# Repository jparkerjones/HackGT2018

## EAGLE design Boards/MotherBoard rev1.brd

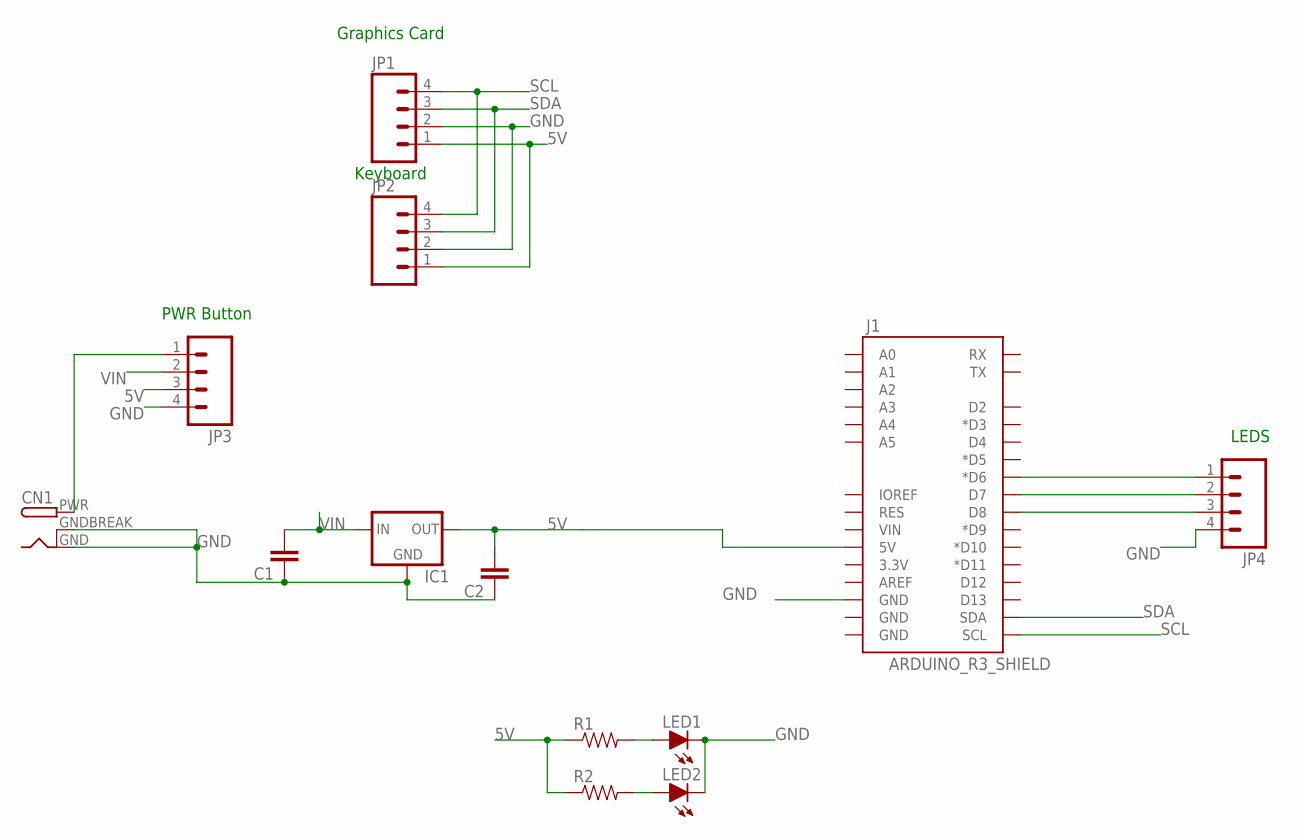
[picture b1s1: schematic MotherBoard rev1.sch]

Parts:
C1, C2: CAPPTH3; CAP-PTH-LARGE
CN1: DCBARRELPTH; DCJACK_2MM_PTH
IC1: 5VREG_L7805SPACED; TO-220-SPACED
J1: ARDUINO_R3_SHIELD; UNO_R3_SHIELD
JP1, JP2, JP3, JP4: M04; 1X04
LED1, LED2: LED-5MM
R1, R2: RESISTORPTH-1/2W; AXIAL-0.5

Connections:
5V: C2.2, IC1.3 (OUT), J1.5V, JP1.1, JP2.1, JP3.3, R1.P$1 (1), R2.P$1 (1)
GND: C1.1, C2.1, CN1.GND, CN1.GNDBREAK, IC1.2 (GND), J1.GND@2 (GND), JP1.2, JP2.2, JP3.4, JP4.4, LED1.K (C), LED2.K (C)
unnamed: LED1.A, R1.P$2 (2)
unnamed: LED2.A, R2.P$2 (2)
unnamed: CN1.PWR, JP3.1
unnamed: J1.D8, JP4.3
unnamed: J1.D6 (*D6), JP4.1
unnamed: J1.D7, JP4.2
SCL: J1.SCL, JP1.4, JP2.4
SDA: J1.SDA, JP1.3, JP2.3
VIN: C1.2, IC1.1 (IN), JP3.2

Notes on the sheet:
Graphics Card
Keyboard
PWR Button
LEDS

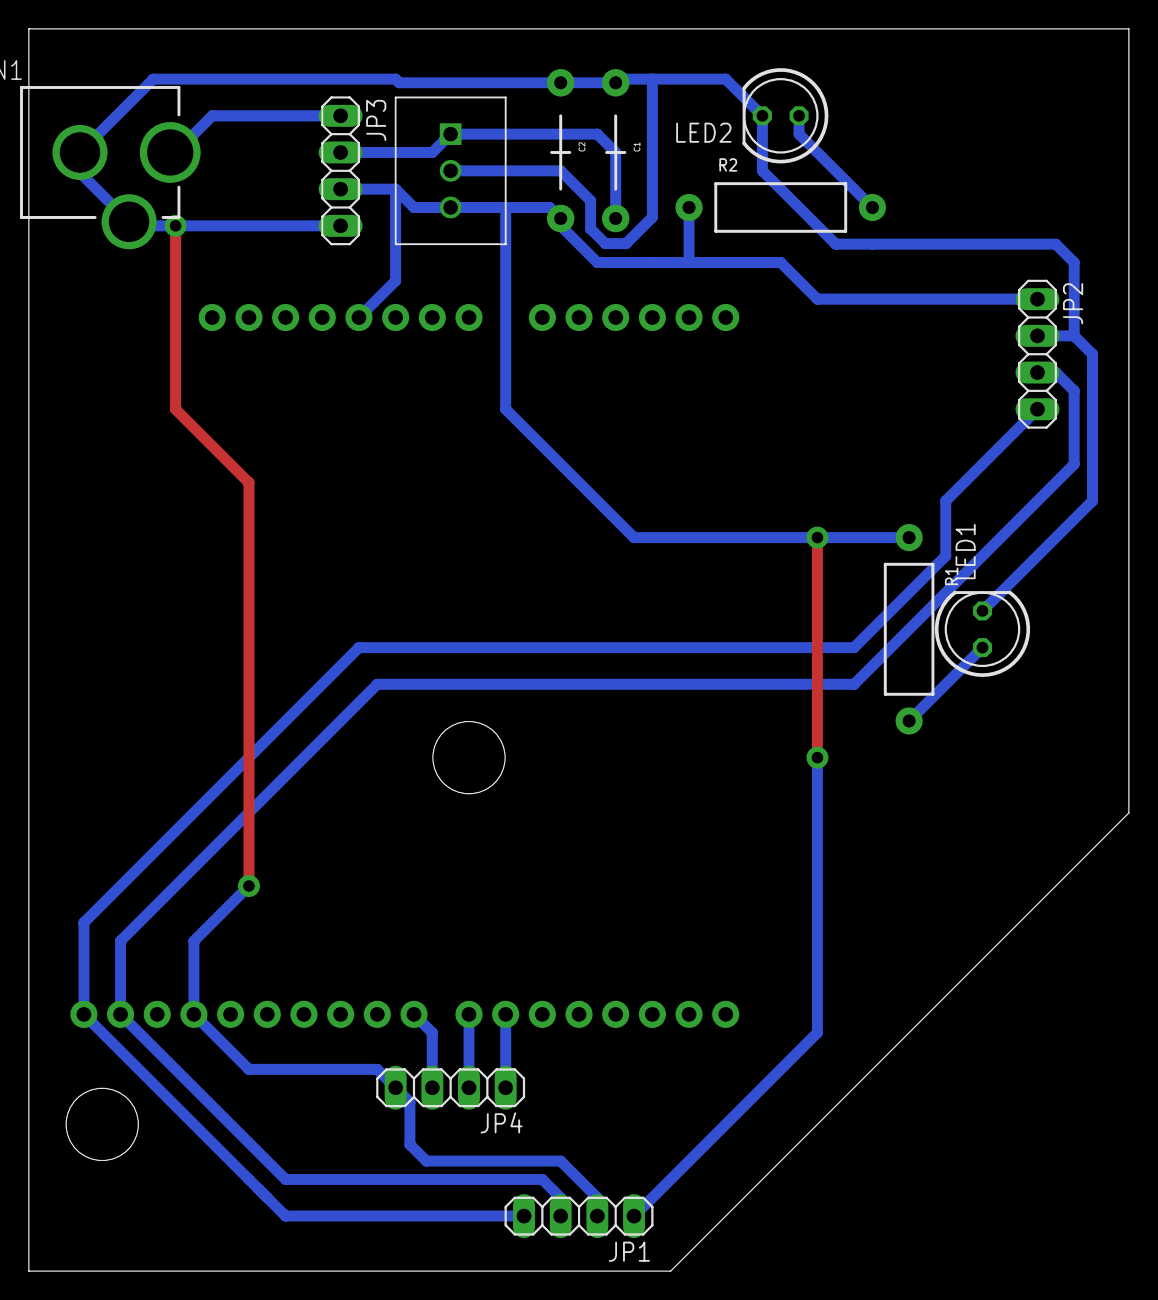
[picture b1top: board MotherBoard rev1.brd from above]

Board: 2 copper layers, 76.2 x 86.0 mm, 13 parts (1 on the bottom side), 11 nets.

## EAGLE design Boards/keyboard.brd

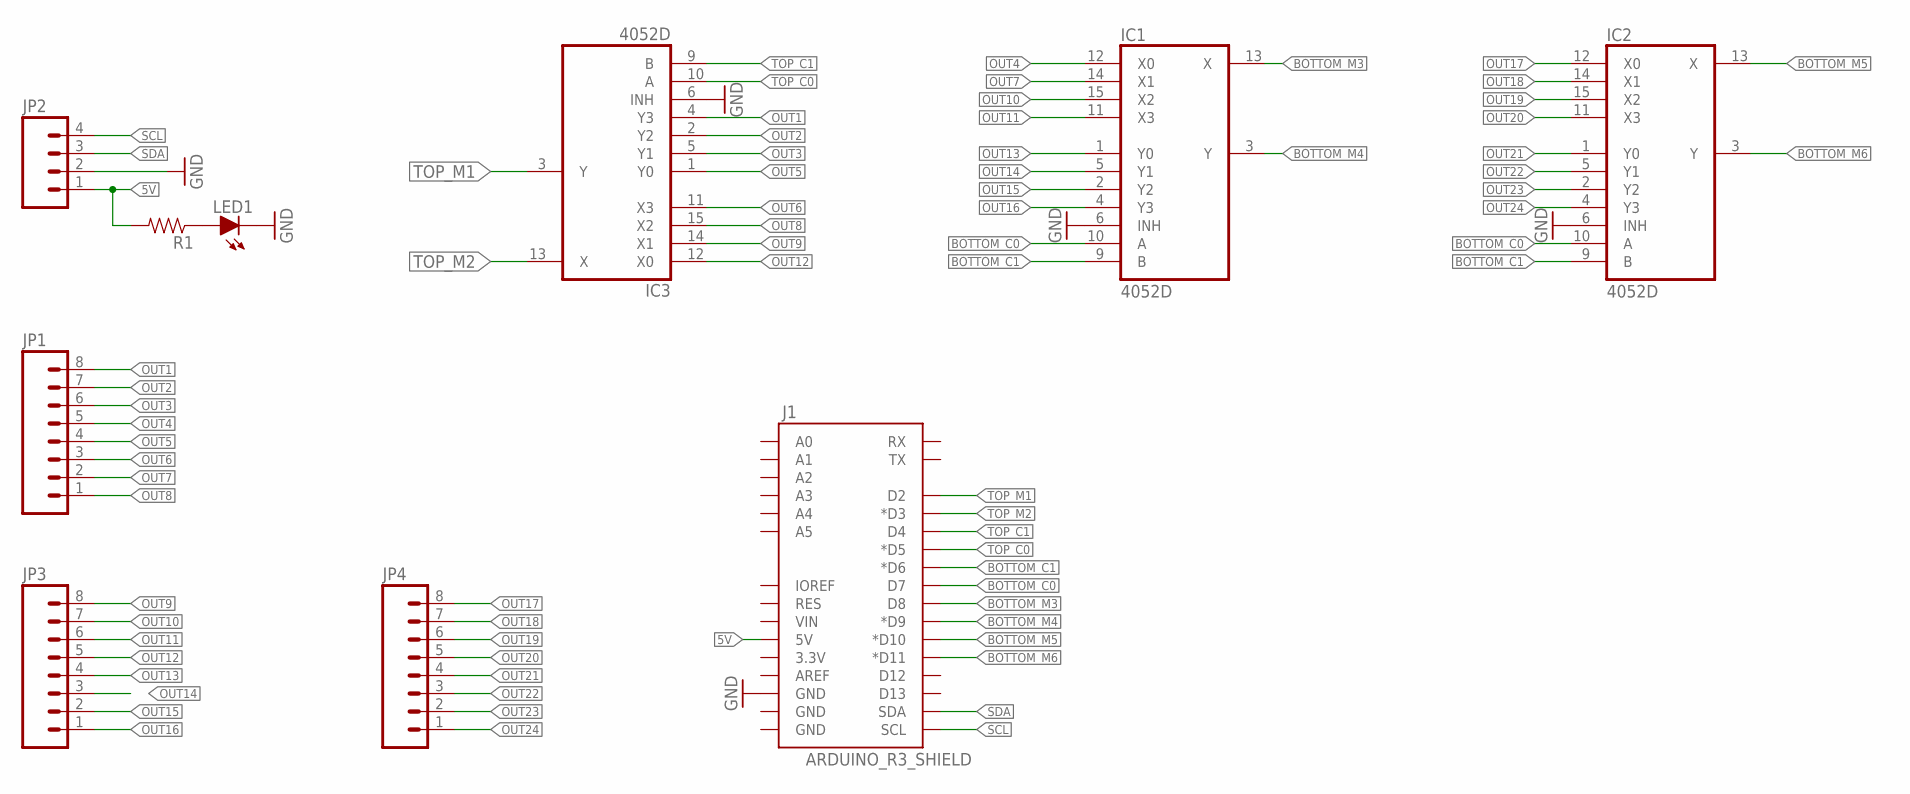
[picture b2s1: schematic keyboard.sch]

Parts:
IC1, IC2, IC3: 4052D; SO16
J1: ARDUINO_R3_SHIELD; UNO_R3_SHIELD
JP1, JP3, JP4: M08; 1X08
JP2: M04; 1X04
LED1: LED-5MM
R1: RESISTORPTH-1/2W; AXIAL-0.5

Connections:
5V: J1.5V, JP2.1, R1.P$2 (2)
BOTTOM_C0: IC1.10 (A), IC2.10 (A), J1.D7
BOTTOM_C1: IC1.9 (B), IC2.9 (B), J1.D6 (*D6)
BOTTOM_M3: IC1.13 (X), J1.D8
BOTTOM_M4: IC1.3 (Y), J1.D9 (*D9)
BOTTOM_M5: IC2.13 (X), J1.D10 (*D10)
BOTTOM_M6: IC2.3 (Y), J1.D11 (*D11)
GND: IC1.6 (INH), IC1.8 (GND), IC2.6 (INH), IC2.8 (GND), IC3.6 (INH), IC3.8 (GND), J1.GND@2 (GND), JP2.2, LED1.K (C)
unnamed: LED1.A, R1.P$1 (1)
OUT1: IC3.4 (Y3), JP1.8
OUT2: IC3.2 (Y2), JP1.7
OUT3: IC3.5 (Y1), JP1.6
OUT4: IC1.12 (X0), JP1.5
OUT5: IC3.1 (Y0), JP1.4
OUT6: IC3.11 (X3), JP1.3
OUT7: IC1.14 (X1), JP1.2
OUT8: IC3.15 (X2), JP1.1
OUT9: IC3.14 (X1), JP3.8
OUT10: IC1.15 (X2), JP3.7
OUT11: IC1.11 (X3), JP3.6
OUT12: IC3.12 (X0), JP3.5
OUT13: IC1.1 (Y0), JP3.4
OUT14: IC1.5 (Y1), JP3.3
OUT15: IC1.2 (Y2), JP3.2
OUT16: IC1.4 (Y3), JP3.1
OUT17: IC2.12 (X0), JP4.8
OUT18: IC2.14 (X1), JP4.7
OUT19: IC2.15 (X2), JP4.6
OUT20: IC2.11 (X3), JP4.5
OUT21: IC2.1 (Y0), JP4.4
OUT22: IC2.5 (Y1), JP4.3
OUT23: IC2.2 (Y2), JP4.2
OUT24: IC2.4 (Y3), JP4.1
SCL: J1.SCL, JP2.4
SDA: J1.SDA, JP2.3
TOP_C0: IC3.10 (A), J1.D5 (*D5)
TOP_C1: IC3.9 (B), J1.D4
TOP_M1: IC3.3 (Y), J1.D2
TOP_M2: IC3.13 (X), J1.D3 (*D3)
VCC: IC1.16 (VCC), IC2.16 (VCC), IC3.16 (VCC)
VEE: IC1.7 (VEE), IC2.7 (VEE), IC3.7 (VEE)

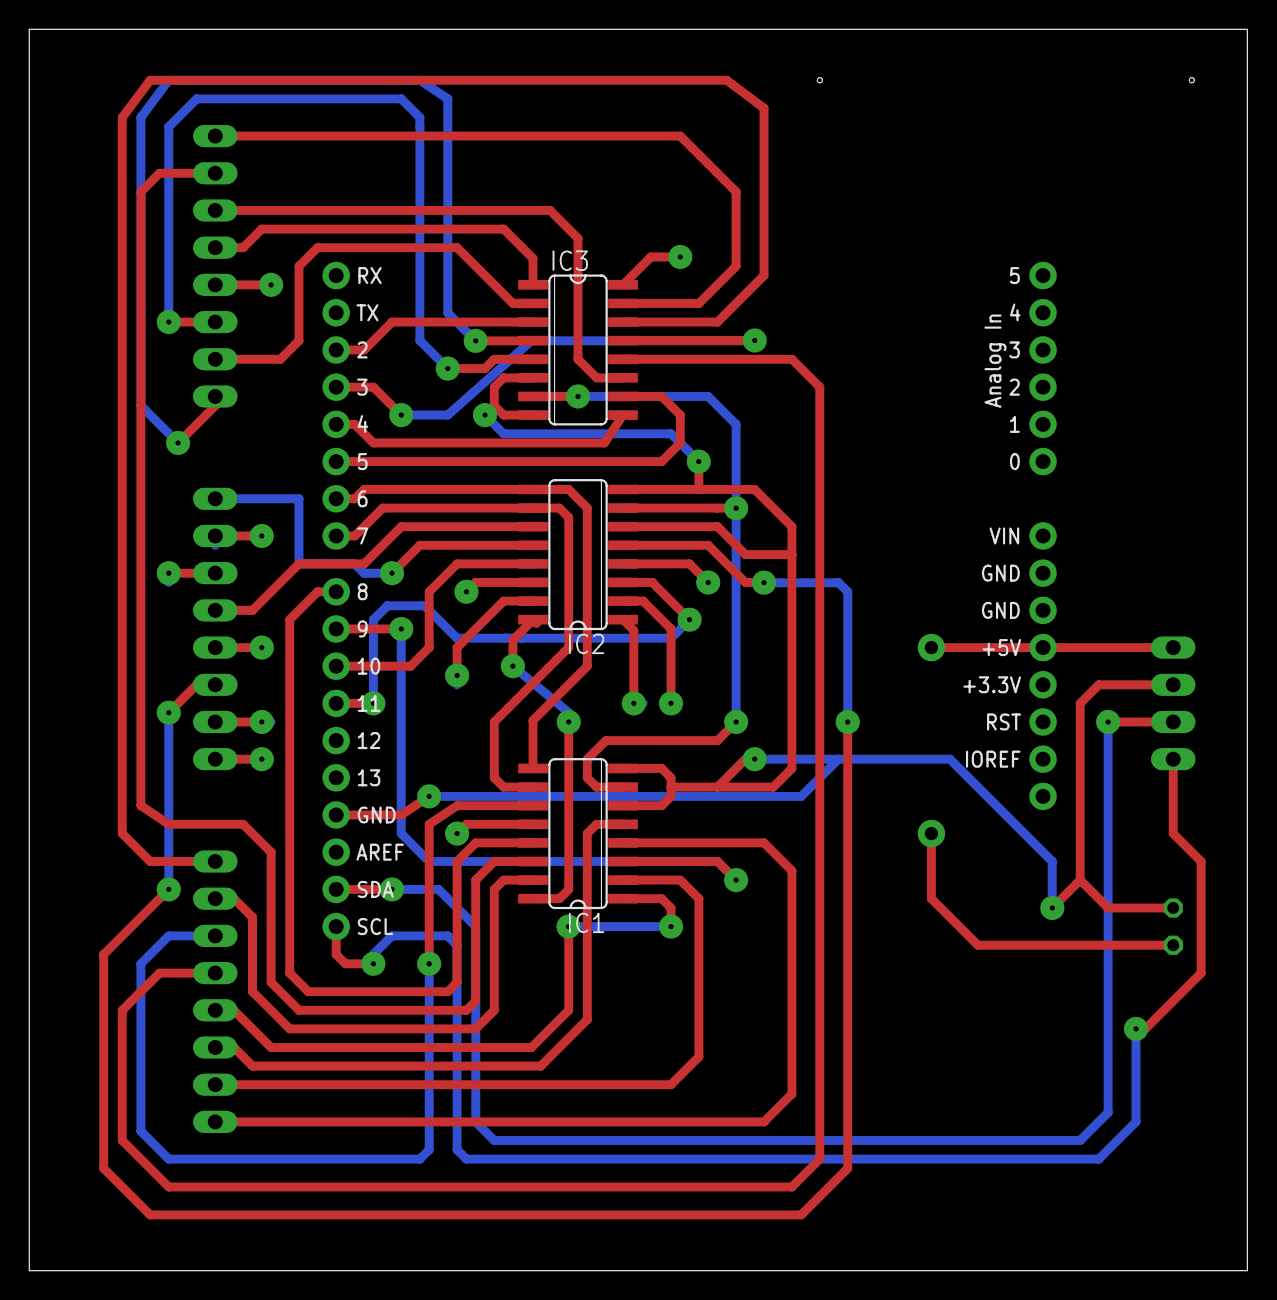
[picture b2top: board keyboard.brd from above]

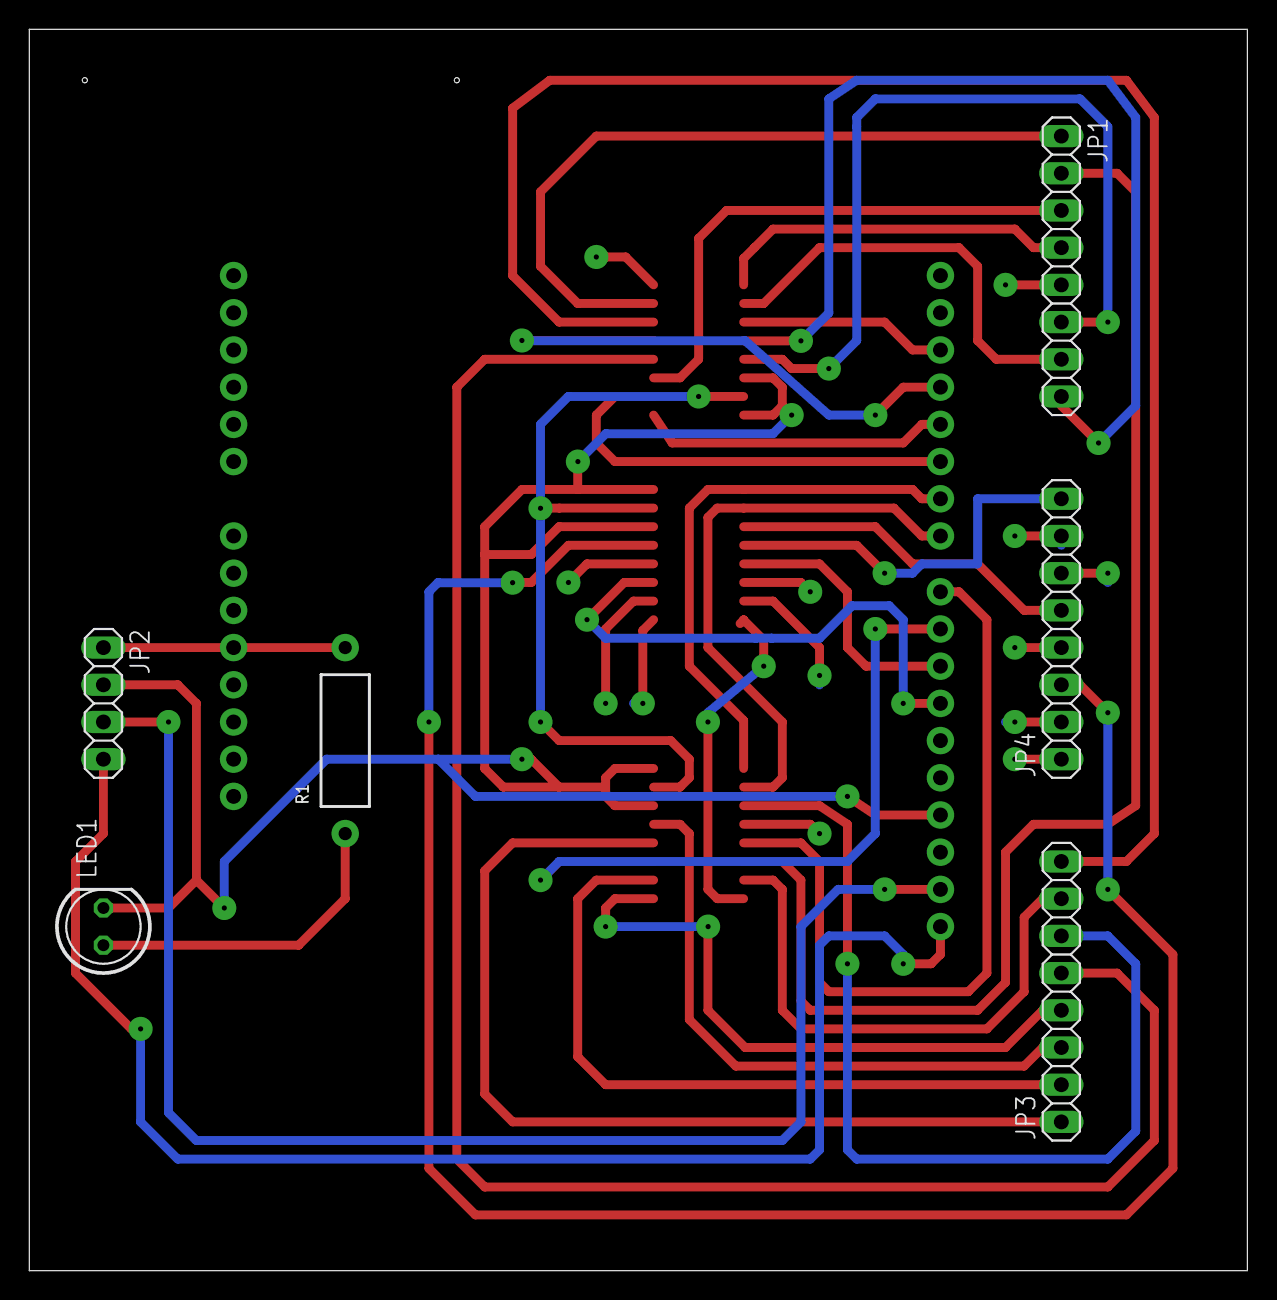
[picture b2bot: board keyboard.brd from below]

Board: 2 copper layers, 83.2 x 84.8 mm, 10 parts (6 on the bottom side), 41 nets.

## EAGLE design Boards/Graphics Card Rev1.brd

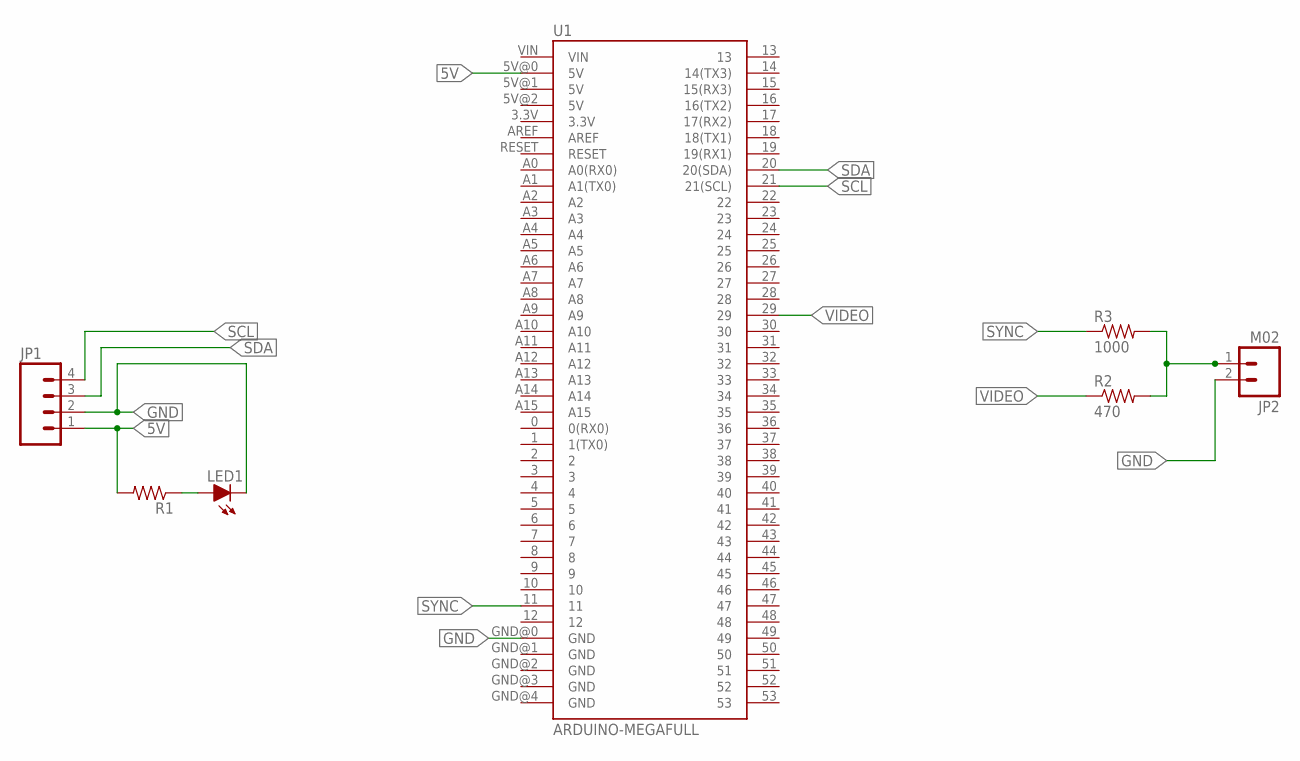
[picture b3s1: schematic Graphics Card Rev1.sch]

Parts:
JP1: M04; 1X04
JP2: M02; 1X02
LED1: LED-5MM
R1: RESISTORPTH-1/2W; AXIAL-0.5
R2: 470; AXIAL-0.5
R3: 1000; AXIAL-0.5
U1: ARDUINO-MEGAFULL; ARDUINO_MEGA

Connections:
5V: JP1.1, R1.P$2 (2), U1.5V@0 (5V)
GND: JP1.2, JP2.2, LED1.K (C), U1.GND@0 (GND)
unnamed: LED1.A, R1.P$1 (1)
unnamed: JP2.1, R2.P$2 (2), R3.P$2 (2)
SCL: JP1.4, U1.21 (21(SCL))
SDA: JP1.3, U1.20 (20(SDA))
SYNC: R3.P$1 (1), U1.11
VIDEO: R2.P$1 (1), U1.29

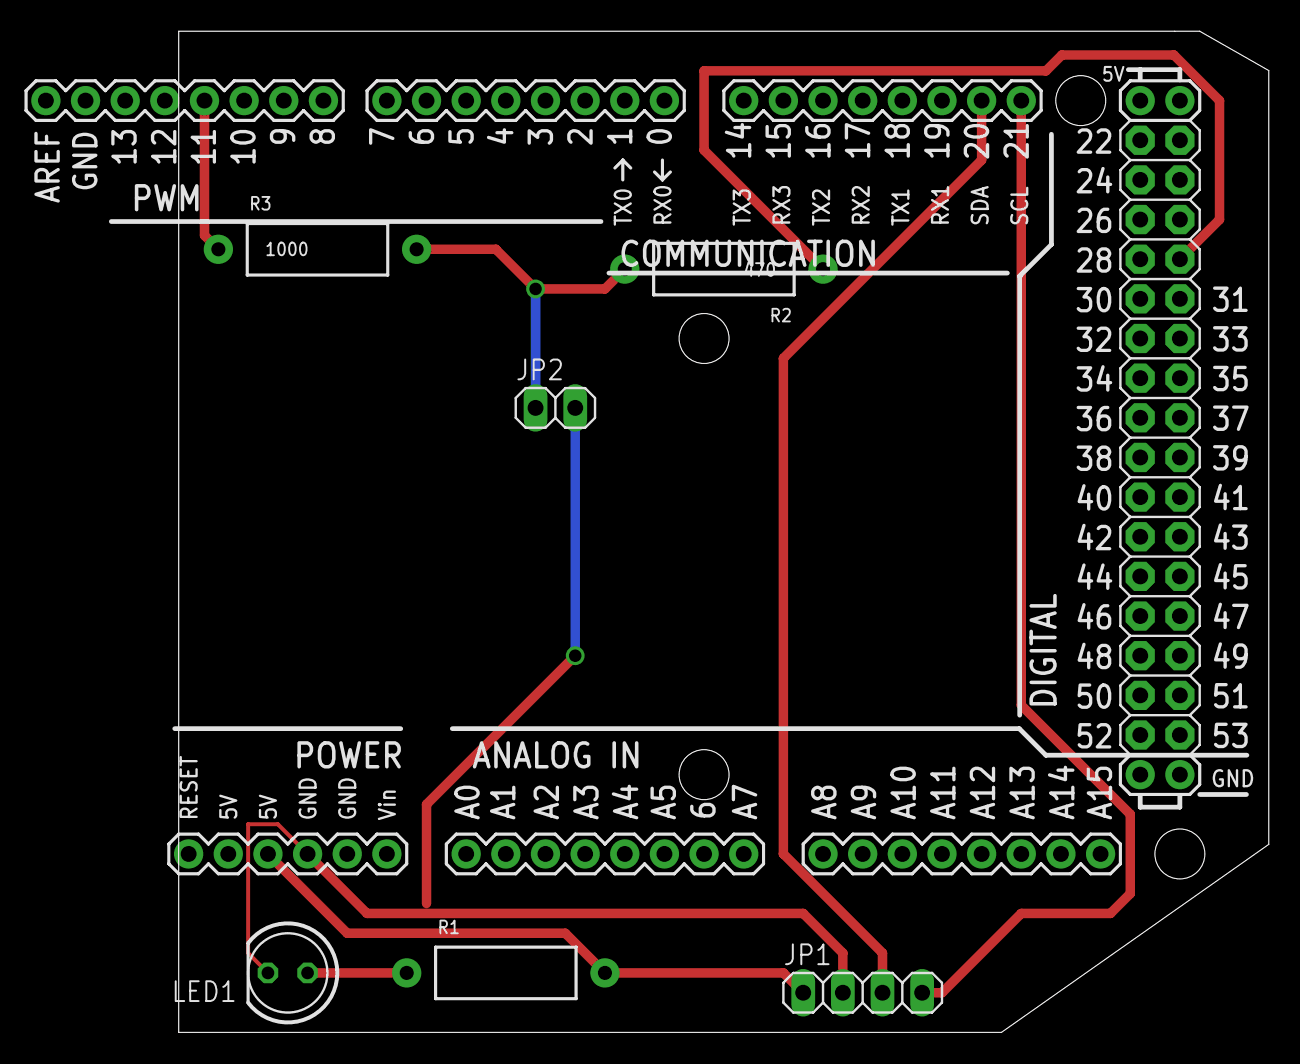
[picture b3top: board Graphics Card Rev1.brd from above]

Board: 2 copper layers, 69.8 x 64.1 mm, 7 parts (0 on the bottom side), 8 nets.

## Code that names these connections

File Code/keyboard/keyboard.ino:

#include <Wire.h>    //I2C library
#define motherboard_addr 8  // I2C address
#define keyboard_addr 9
#define graphics_addr 10

// assign pin numbers
int top_m1 = 13;
int top_m1_c1 = 12;
int top_m1_c0 = 11;

int top_m2 = 10;
int top_m2_c1 = 9;
int top_m2_c0 = 8;

int bottom_c1 = 7;
int bottom_c0 = 6;
int bottom_m3 = 5;
int bottom_m4 = 4;
int bottom_m5 = 3;
int bottom_m6 = 2;

int key_map_matrix[8][16] = {
 {0, 0, 0, 27, 0, 71, 0, 72, 0, 0, 0, 0, 8, 0, 39, 0},
 {0, 0, 87, 81, 69, 82, 0, 85, 73, 0, 0, 0, 0, 79, 80},
 {0, 0, 50, 49, 51, 52, 0, 54, 55, 0, 0, 0, 0, 57, 48, 0},
 {0, 0, 83, 65, 68, 70, 0, 74, 75, 0, 0, 0, 0, 76, 59, 0},
 {0, 0, 88, 90, 67, 86, 0, 77, 60, 0, 0, 0, 32, 62, 47, 0},
 {0, 0, 0, 9, 0, 84, 0, 89, 74, 0, 0, 0, 0, 0, 91, 0},
 {0, 0, 0, 0, 0, 66, 0, 78, 0, 0, 0, 0, 0, 0, 61, 127}
 }; // [top_wire][bottom_wire] = ASCII value of key_pressed

void setup() {
  Wire.begin(keyboard_addr);
  Serial.begin(9600);

  for (int i = 13; i >= 6; i--) {
    pinMode(i, OUTPUT);
  }

  for (int i = 5; i >= 2; i--) {
    pinMode(i, INPUT);
  }

}

byte x = 0;

void loop() {
  int key_pressed = decode_key();
  if (key_pressed != 0) {
    Wire.beginTransmission(motherboard_addr);   // transmit to device #8
    Wire.write("keyboard is ");           // sends five bytes
    Wire.write(x);                        // sends one byte
    Wire.endTransmission();               // stop transmitting
    Serial.print(x);
    x++;
  }
  
  delay(500);
}

int decode_key() {
  
  for (int m = 0; m <= 1; m++) { // check both mux
    if (m == 0) {
      digitalWrite(top_m1, HIGH); // check mux1 input
      digitalWrite(top_m2, LOW);
    } else {
      digitalWrite(top_m1, LOW);  // check mux2 input
      digitalWrite(top_m2, HIGH);
    }
    
    for (int i = 0; i < 4; i++) {     // set out2 - out5 high one at a time
      if (m == 0) {
        digitalWrite(top_m1_c1, i/2);
        digitalWrite(top_m1_c0, i%2);
      } else {
        digitalWrite(top_m2_c1, i/2);
        digitalWrite(top_m2_c0, i%2);
      }
      
  
      for (int c = 0; c < 4; c++) {   // set the control signals for bottom layer
        digitalWrite(bottom_c1, i/2);
        digitalWrite(bottom_c0, i%2);
  
        if (digitalRead(bottom_m3)) { // something is connected to M3 
          switch (c){
            case 0: // out4
              return key_map_matrix[i + 4 * m][0];
            case 1: // out7
              return key_map_matrix[i + 4 * m][1];
            case 2: // out10
              return key_map_matrix[i + 4 * m][2];
            case 3: // out11
              return key_map_matrix[i + 4 * m][3];
          }
        }
  
         if (digitalRead(bottom_m4)) { // something is connected to M4 
          switch (c) {
            case 0: // out13
              return key_map_matrix[i + 4 * m][4];
            case 1: // out14
              return key_map_matrix[i + 4 * m][5];
            case 2: // out15
              return key_map_matrix[i + 4 * m][6];
            case 3: // out16
              return key_map_matrix[i + 4 * m][7];
          }
        }
  
         if (digitalRead(bottom_m5)) { // something is connected to M5
          switch (c){
            case 0: // out17
              return key_map_matrix[i + 4 * m][8];
            case 1: // out18
              return key_map_matrix[i + 4 * m][9];
            case 2: // out19
              return key_map_matrix[i + 4 * m][10];
            case 3: // out20
              return key_map_matrix[i + 4 * m][11];
           }
        }
  
         if (digitalRead(bottom_m6)) { // something is connected to M6 
          switch (c){
            case 0: // out21
              return key_map_matrix[i + 4 * m][12];
            case 1: // out22
              return key_map_matrix[i + 4 * m][13];
            case 2: // out23
              return key_map_matrix[i + 4 * m][14];
            case 3: // out24
              return key_map_matrix[i + 4 * m][15];
          }
        }
      }
    }
  }
  
  return 0;
}

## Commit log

2018-10-20 I2C Test Files
2018-10-20 Mapped keyboard pins
2018-10-20 Working I2C send and recieve
2018-10-20 Keyboard BreakoutRev1
2018-10-20 Working 3-way I2C communication
    Very basic code for the keyboard, motherboard, and graphics arduino. Keyboard will transmits to motherboard, motherboard recieves and transmits to graphics.
2018-10-20 added TVout
2018-10-21 Graphics Card Board Rev1
2018-10-21 Updated keyboard mapping and code
    Mapped the value of the key with its corresponding top & bottom layer pinouts into a matrix. Updated keyboard code to read the key pressed
2018-10-21 Motherboard Schematic
2018-10-21 Keyboard BreakoutRev2
2018-10-21 Rev1Testing of Graphics card
2018-10-21 keyboard readout board with muxes
2018-10-21 arduino linux penguin logo
2018-10-21 Revised logo with transparent background
2018-10-21 Presentation Code
2018-10-21 Updates for Yun Motherboard code
